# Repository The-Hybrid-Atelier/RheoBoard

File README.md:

# Start here: [Wiki](https://github.com/The-Hybrid-Atelier/RheoBoard/wiki)

- [What is REP?](https://github.com/The-Hybrid-Atelier/RheoBoard/wiki/What-is-REP)
- [Sensing Setup](https://github.com/The-Hybrid-Atelier/RheoBoard/wiki/Sensing-Setup)
- [Build options](https://github.com/The-Hybrid-Atelier/RheoBoard/wiki/Build-options)
- [Current PCB (v2) and earlier revisions](RheoBoard_PCB/README.md)

## RheoBoard

RheoBoard is open hardware for pneumatic retraction-extrusion measurements. On command, it runs a REP (retraction-extrusion pulse) and streams the pressure trace.

## License

All license notices are consolidated in [`LICENSE`](LICENSE):

- Hardware designs: CERN-OHL-W-2.0
- Firmware: MIT
- Documentation: [CC BY-SA 4.0](https://creativecommons.org/licenses/by-sa/4.0/)

RheoBoard project version 1 is certified open source hardware by the Open Source Hardware Association,
UID [US002865](https://certification.oshwa.org/us002865.html); details are on the
[Certification](https://github.com/The-Hybrid-Atelier/RheoBoard/wiki/Certification) page.
Machine-readable project metadata and the current version are in
[`okh-RheoBoard.yml`](okh-RheoBoard.yml).

## Authors

This project was created and maintained by [Cesar Torres](https://www.cearto.com) and [Charlie Vuong](https://charlie-vuong.com/) (The Hybrid Atelier at UT Arlington).

> **RheoBoard is part of [Rheoverse](https://rheoverse.cearto.com/)**, the public platform for the NSF CAREER project “Towards Interactive Sensor-Driven Tools for Exploring, Replicating, and Sharing Material Recipes” ([Award 2543683](https://www.nsf.gov/awardsearch/show-award?AWD_ID=2543683)).

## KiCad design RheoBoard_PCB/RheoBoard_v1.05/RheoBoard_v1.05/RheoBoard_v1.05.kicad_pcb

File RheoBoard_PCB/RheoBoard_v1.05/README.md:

# RheoBoard v1.05

Ordering notes for this revision are on the [BOM](https://github.com/The-Hybrid-Atelier/RheoBoard/wiki/BOM) page. Open `RheoBoard_v1.05/RheoBoard_v1.05.kicad_pro`. The main schematic and PCB use that same stem. Other schematics beside them are standalone block references or stubs, not the project hierarchy.

- Revision notes: `REVISION_NOTES.md`
- BOM: `BOM/README.md`
- Assembly and bringup: `ASSEMBLY_AND_BRINGUP.md` (button cable, GPIO map, and PCA register settings)
- Manufacturing files: `Manufacturing/README.md`
- `Archive_v1_outputs/` holds the historical v1 outputs, including the original assembly workbook `Archive_v1_outputs/BOM/BOM_RheoboardV1_JLCSMT.xlsx`

This remains an untested hardware revision. Supplier placement review and physical electrical, thermal, and mechanical qualification remain open. The maintainer accepted the retained sensor-reset and valve-voltage-margin risks for this prototype; that acceptance is not a measured hardware result or repeated-production approval. The repository DIY sketch is not verified compatible with this actuator interface.

Hardware design licensing follows the repository root LICENSE, CERN-OHL-W-2.0. Documentation is CC BY-SA 4.0.

The inner project folder was renamed from `RheoboardV1` to `RheoBoard_v1.05` on 2026-10-22. Source contents and revision are unchanged.

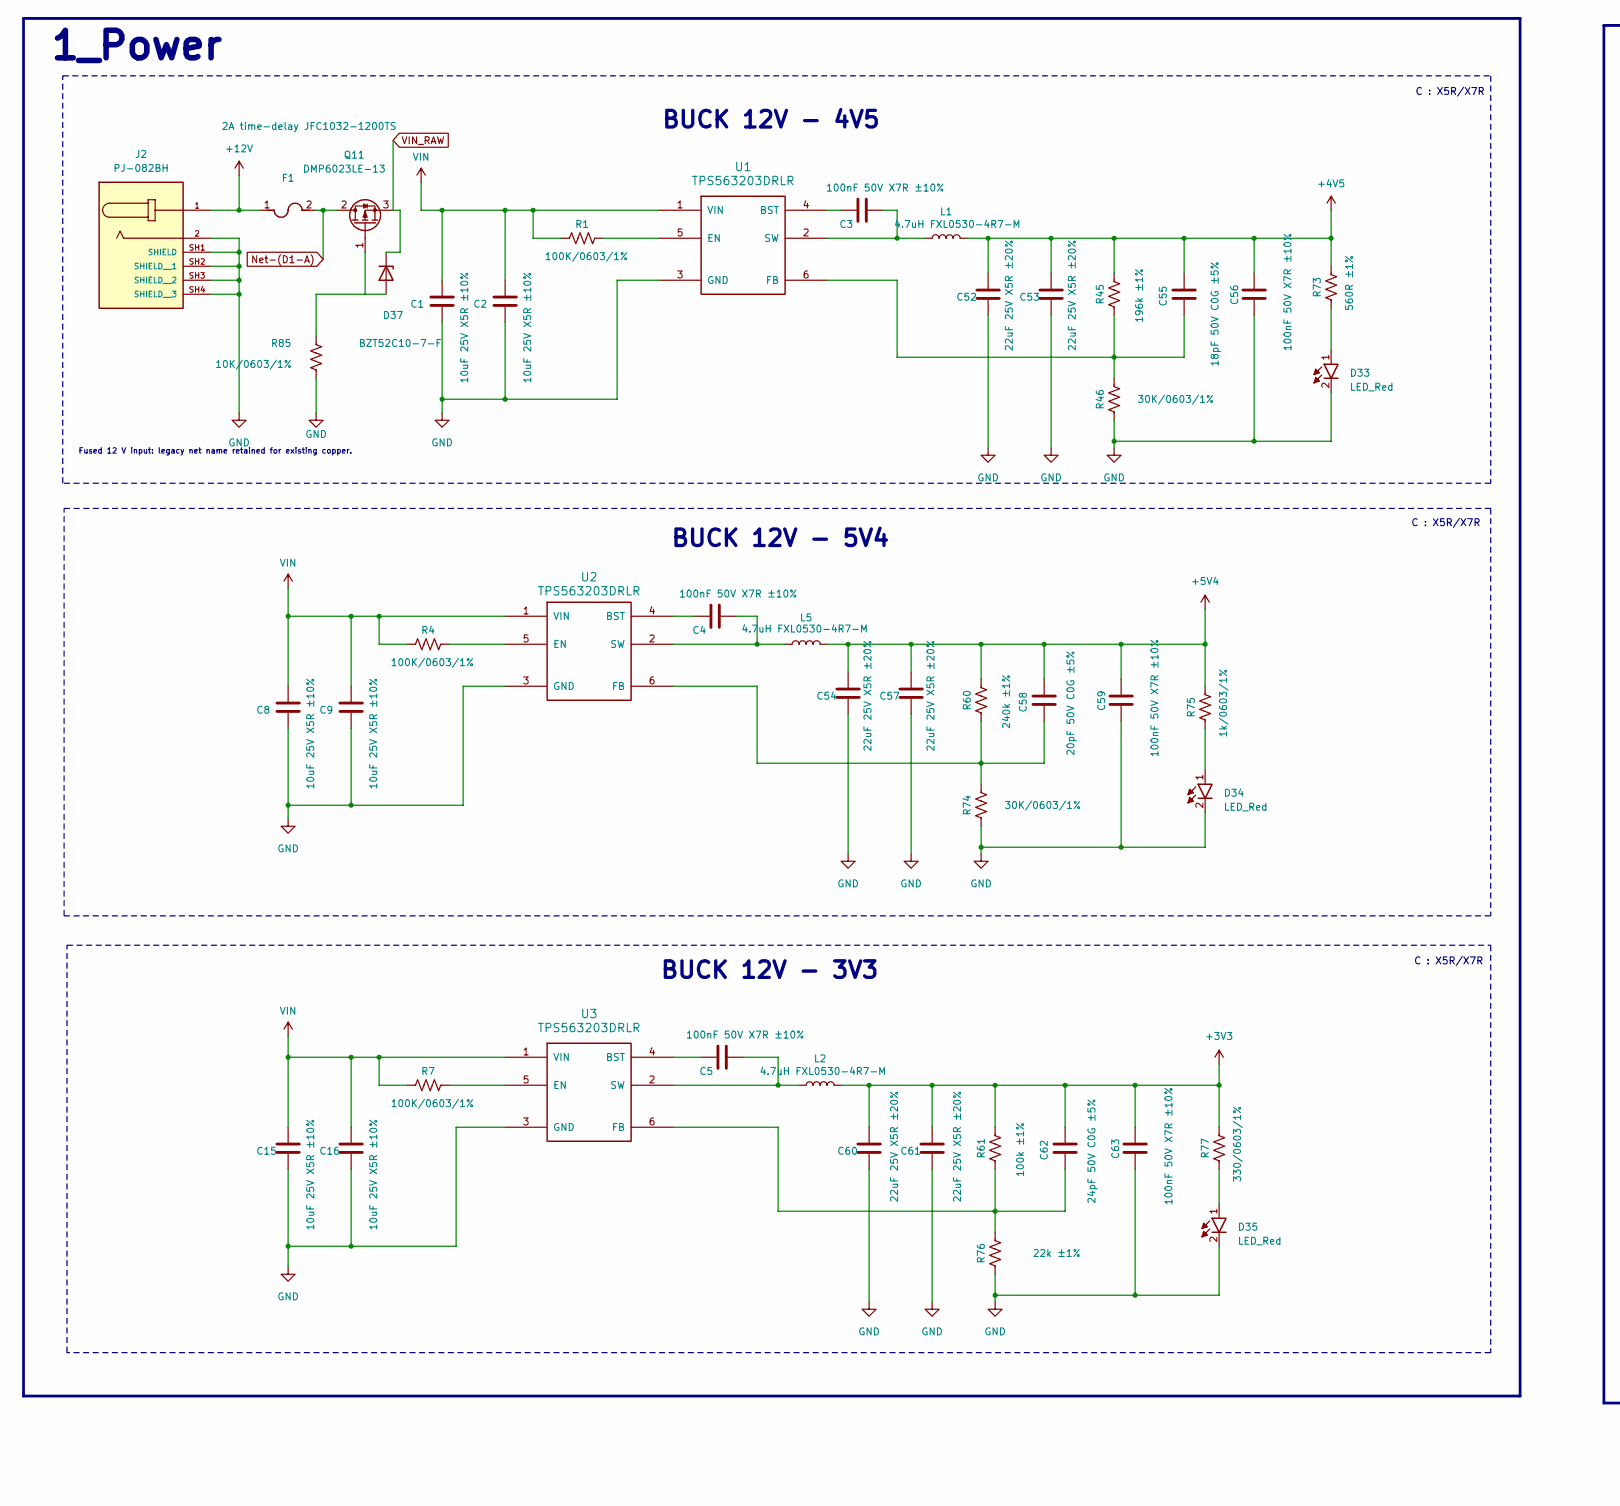
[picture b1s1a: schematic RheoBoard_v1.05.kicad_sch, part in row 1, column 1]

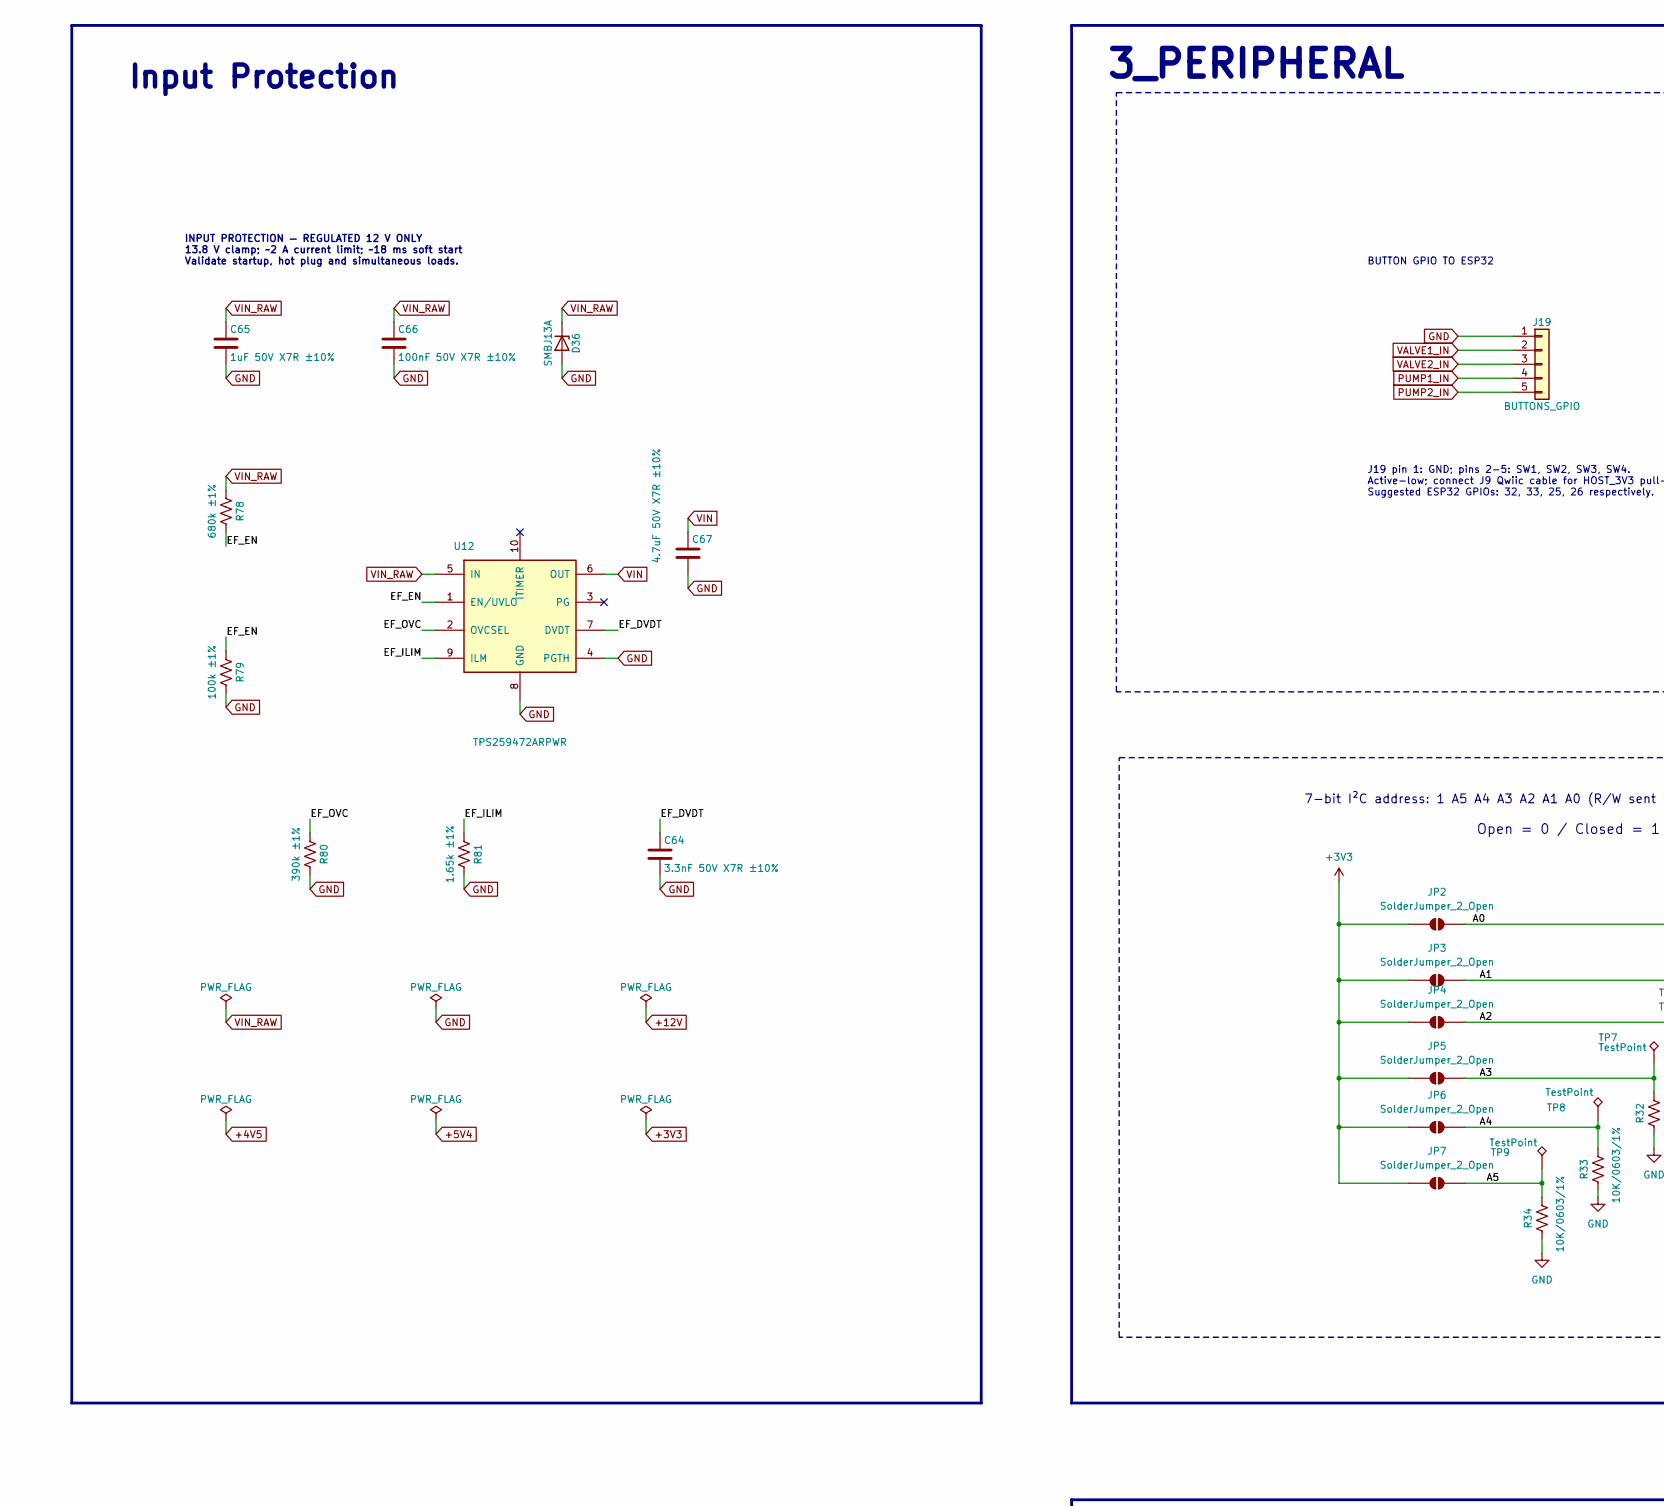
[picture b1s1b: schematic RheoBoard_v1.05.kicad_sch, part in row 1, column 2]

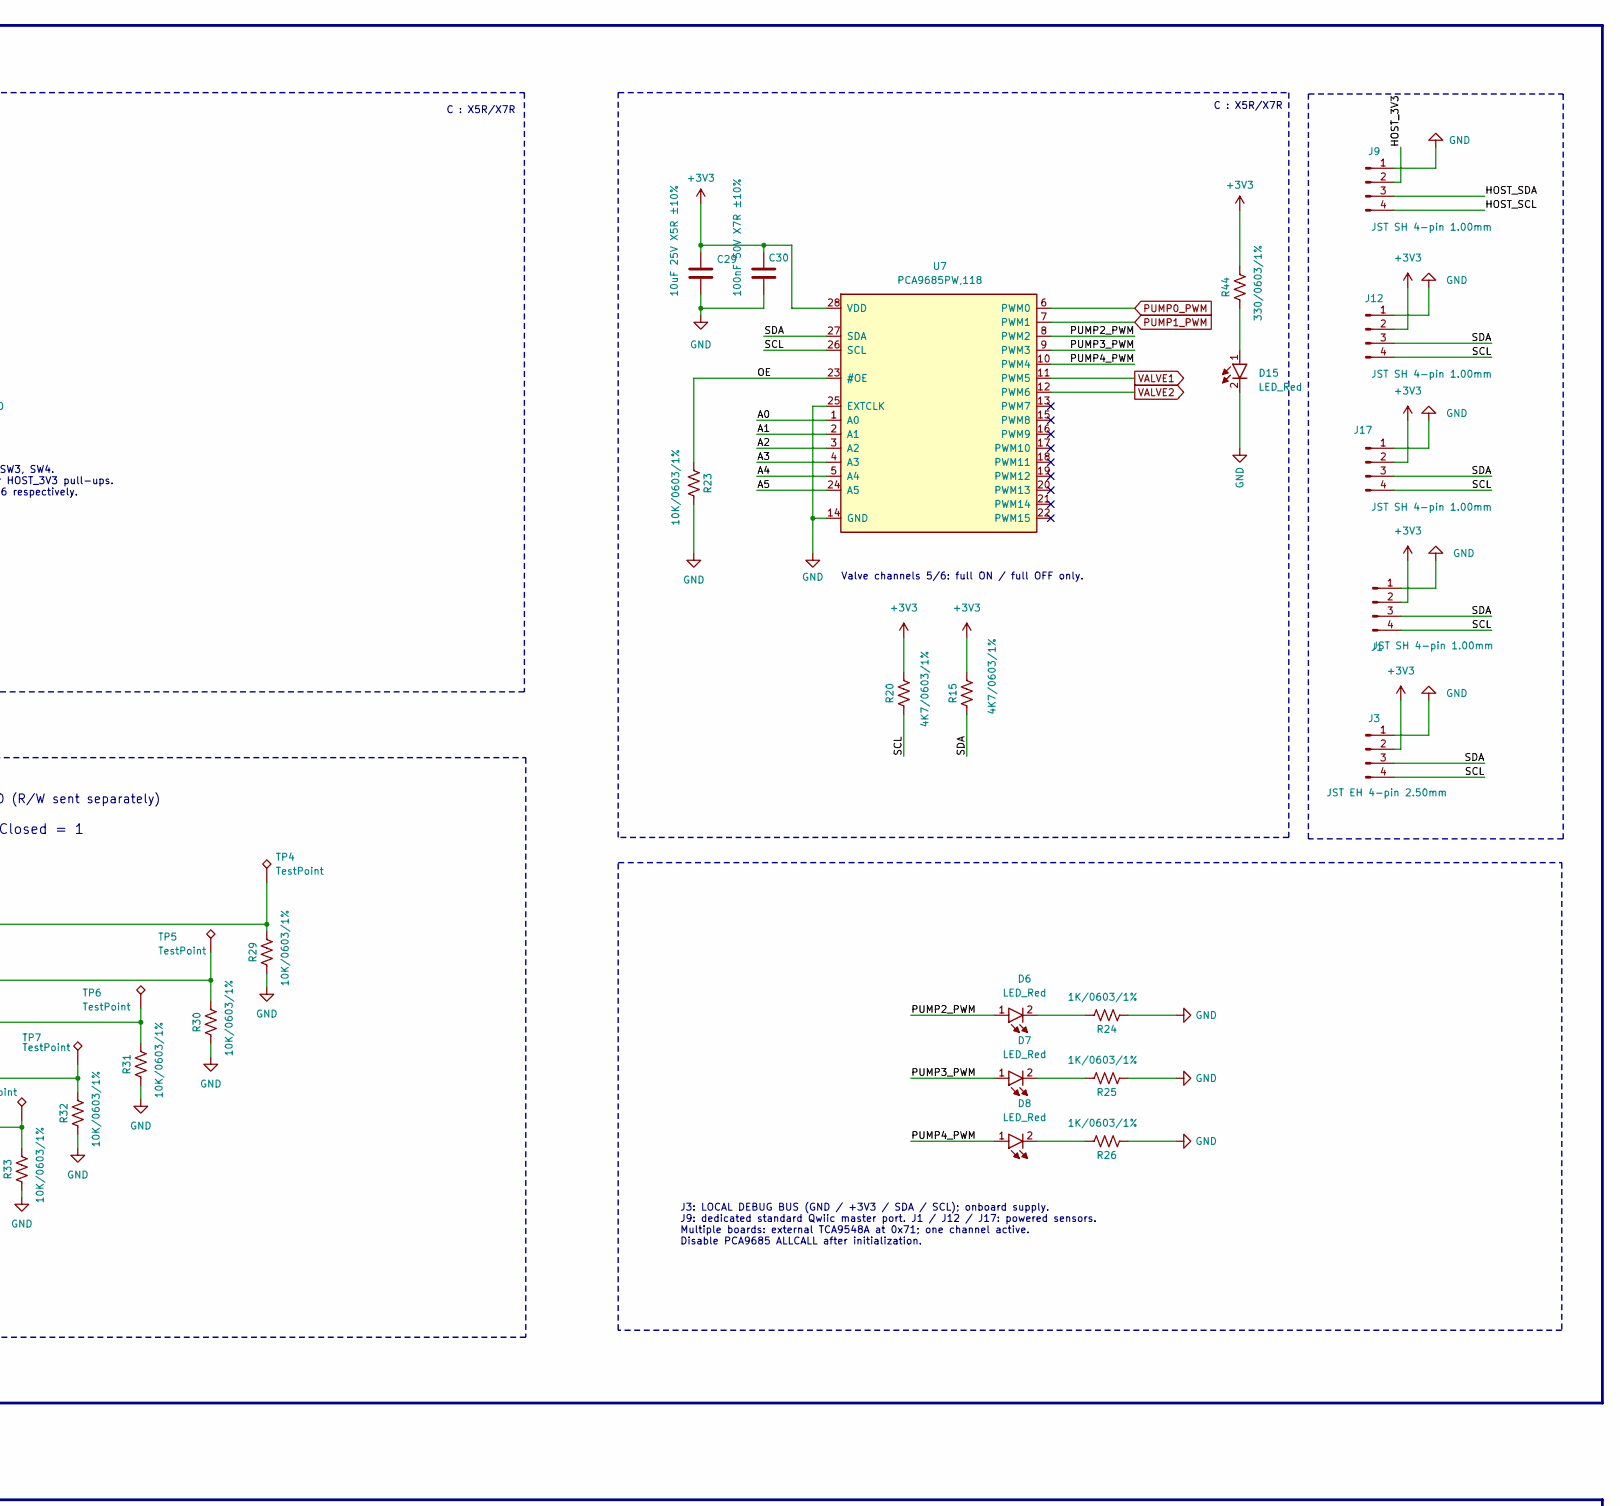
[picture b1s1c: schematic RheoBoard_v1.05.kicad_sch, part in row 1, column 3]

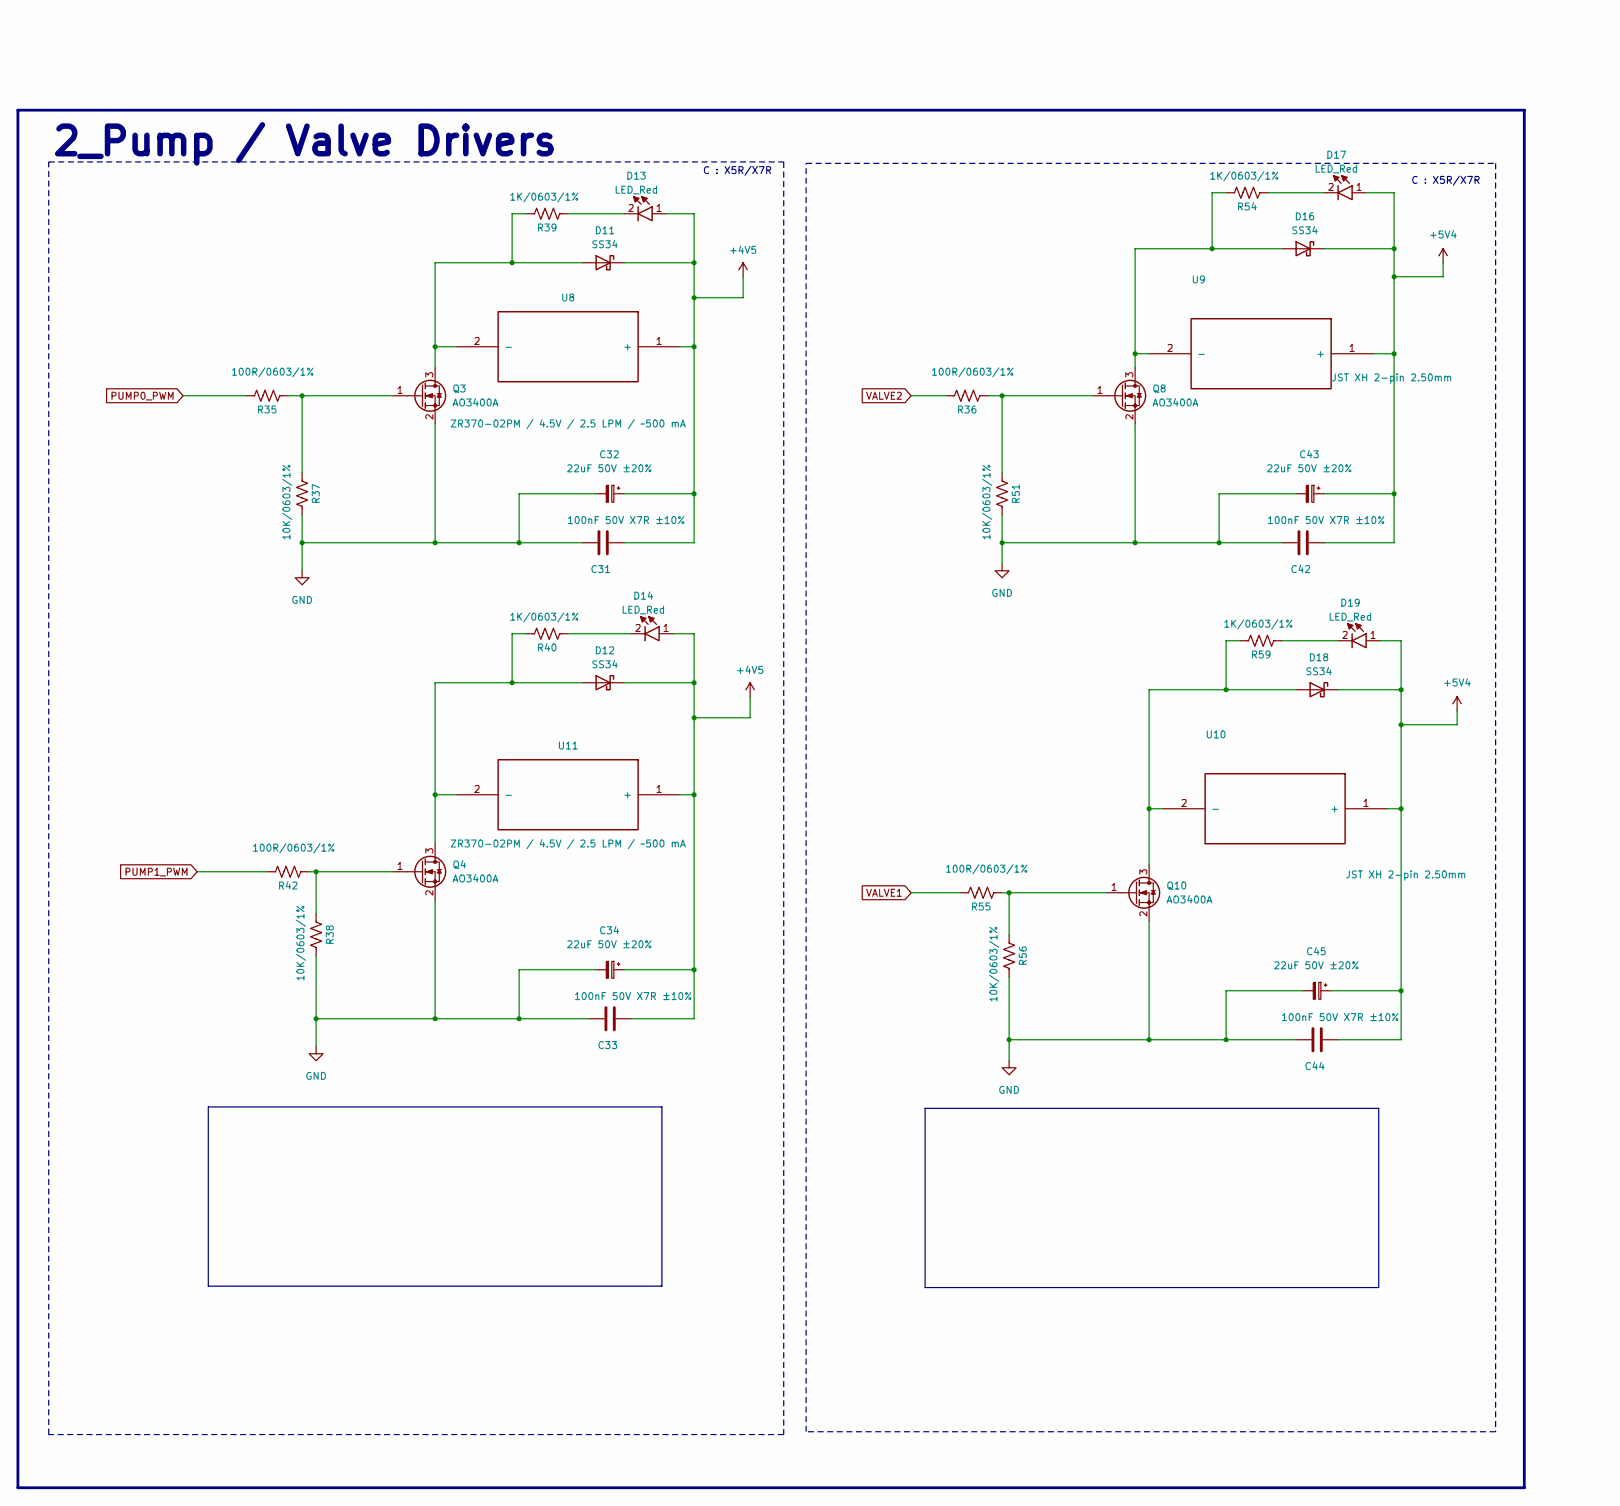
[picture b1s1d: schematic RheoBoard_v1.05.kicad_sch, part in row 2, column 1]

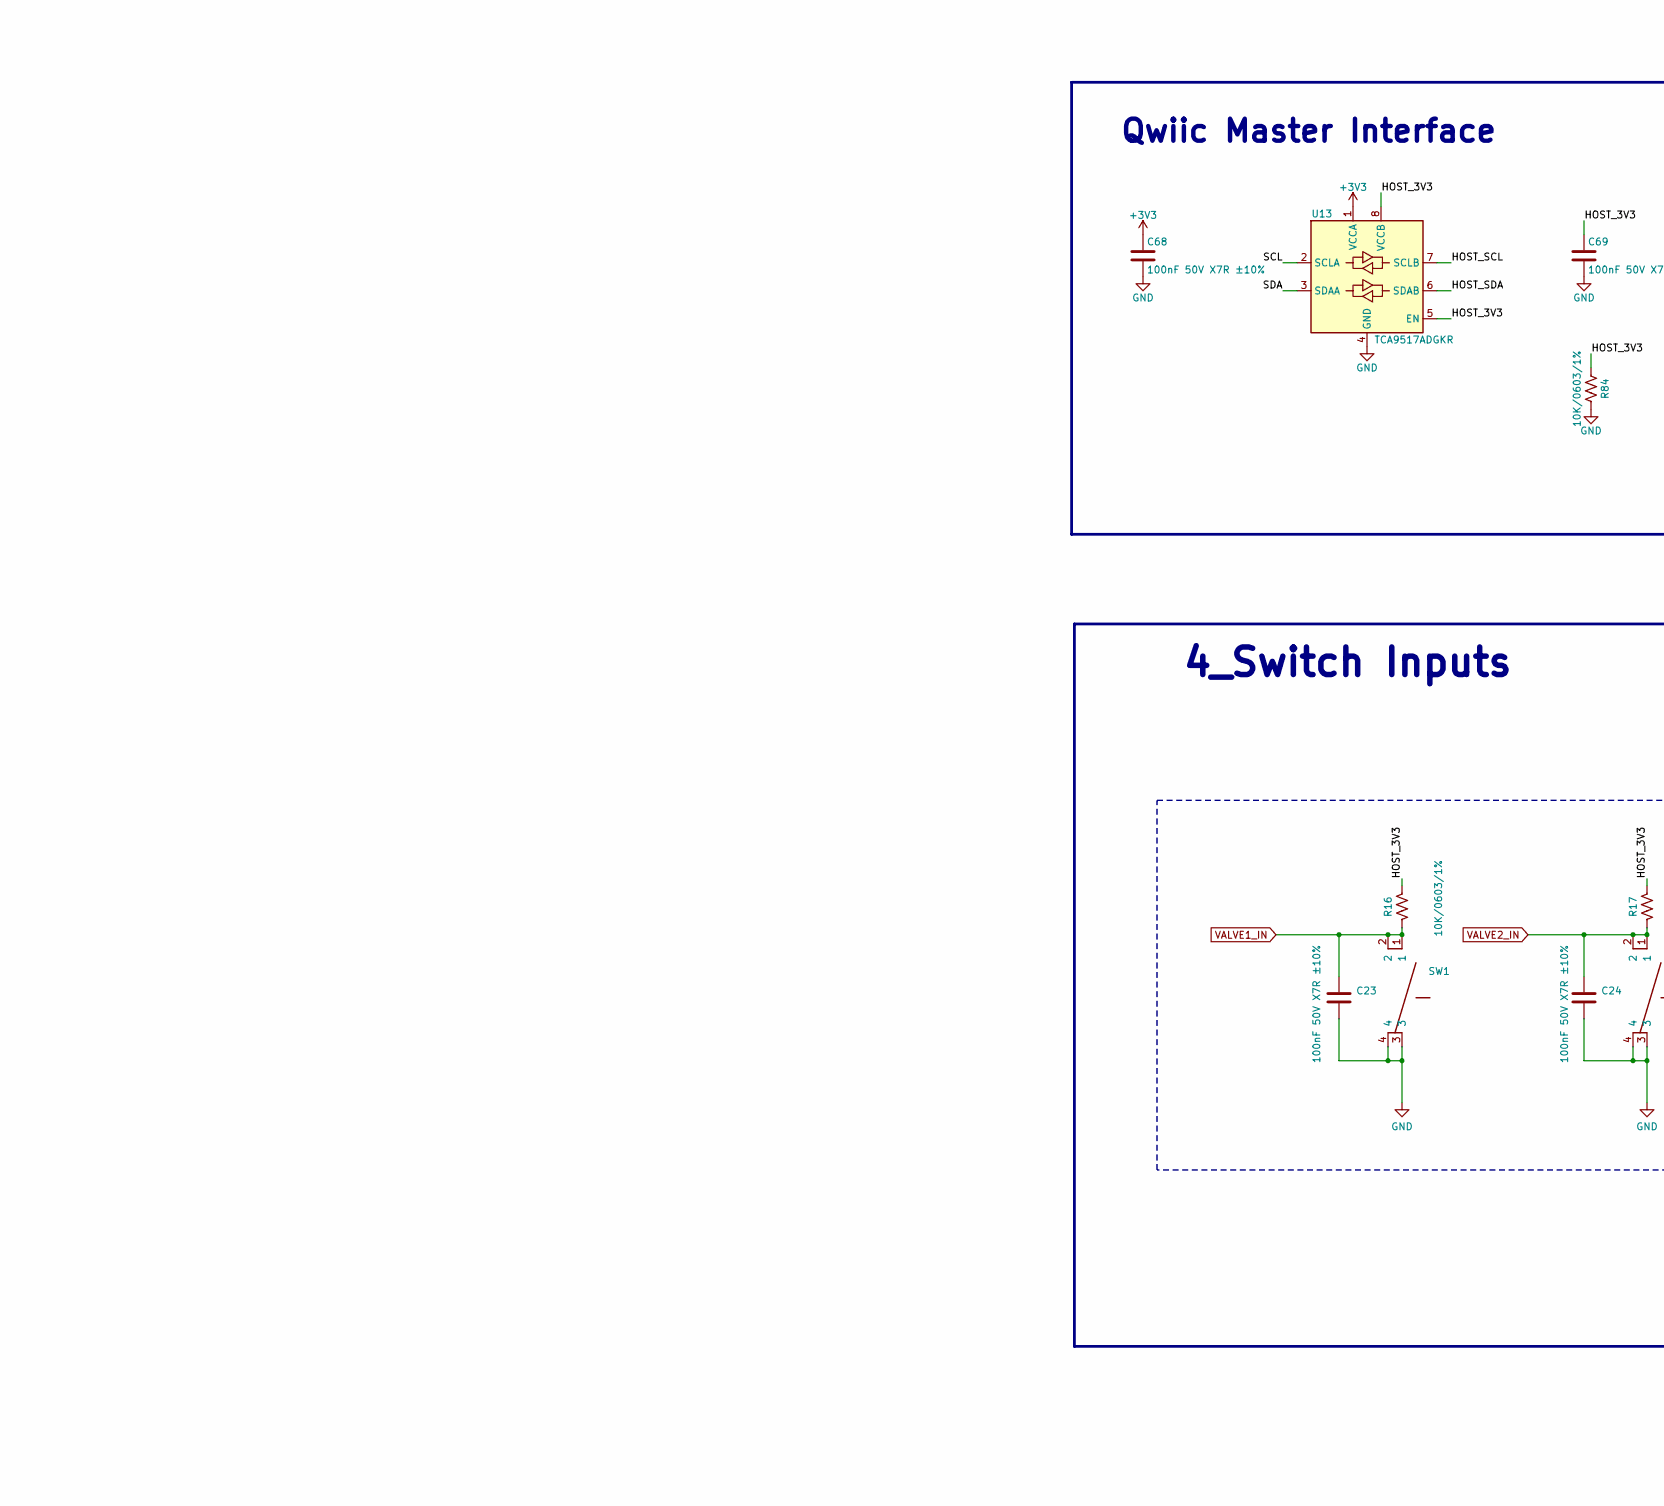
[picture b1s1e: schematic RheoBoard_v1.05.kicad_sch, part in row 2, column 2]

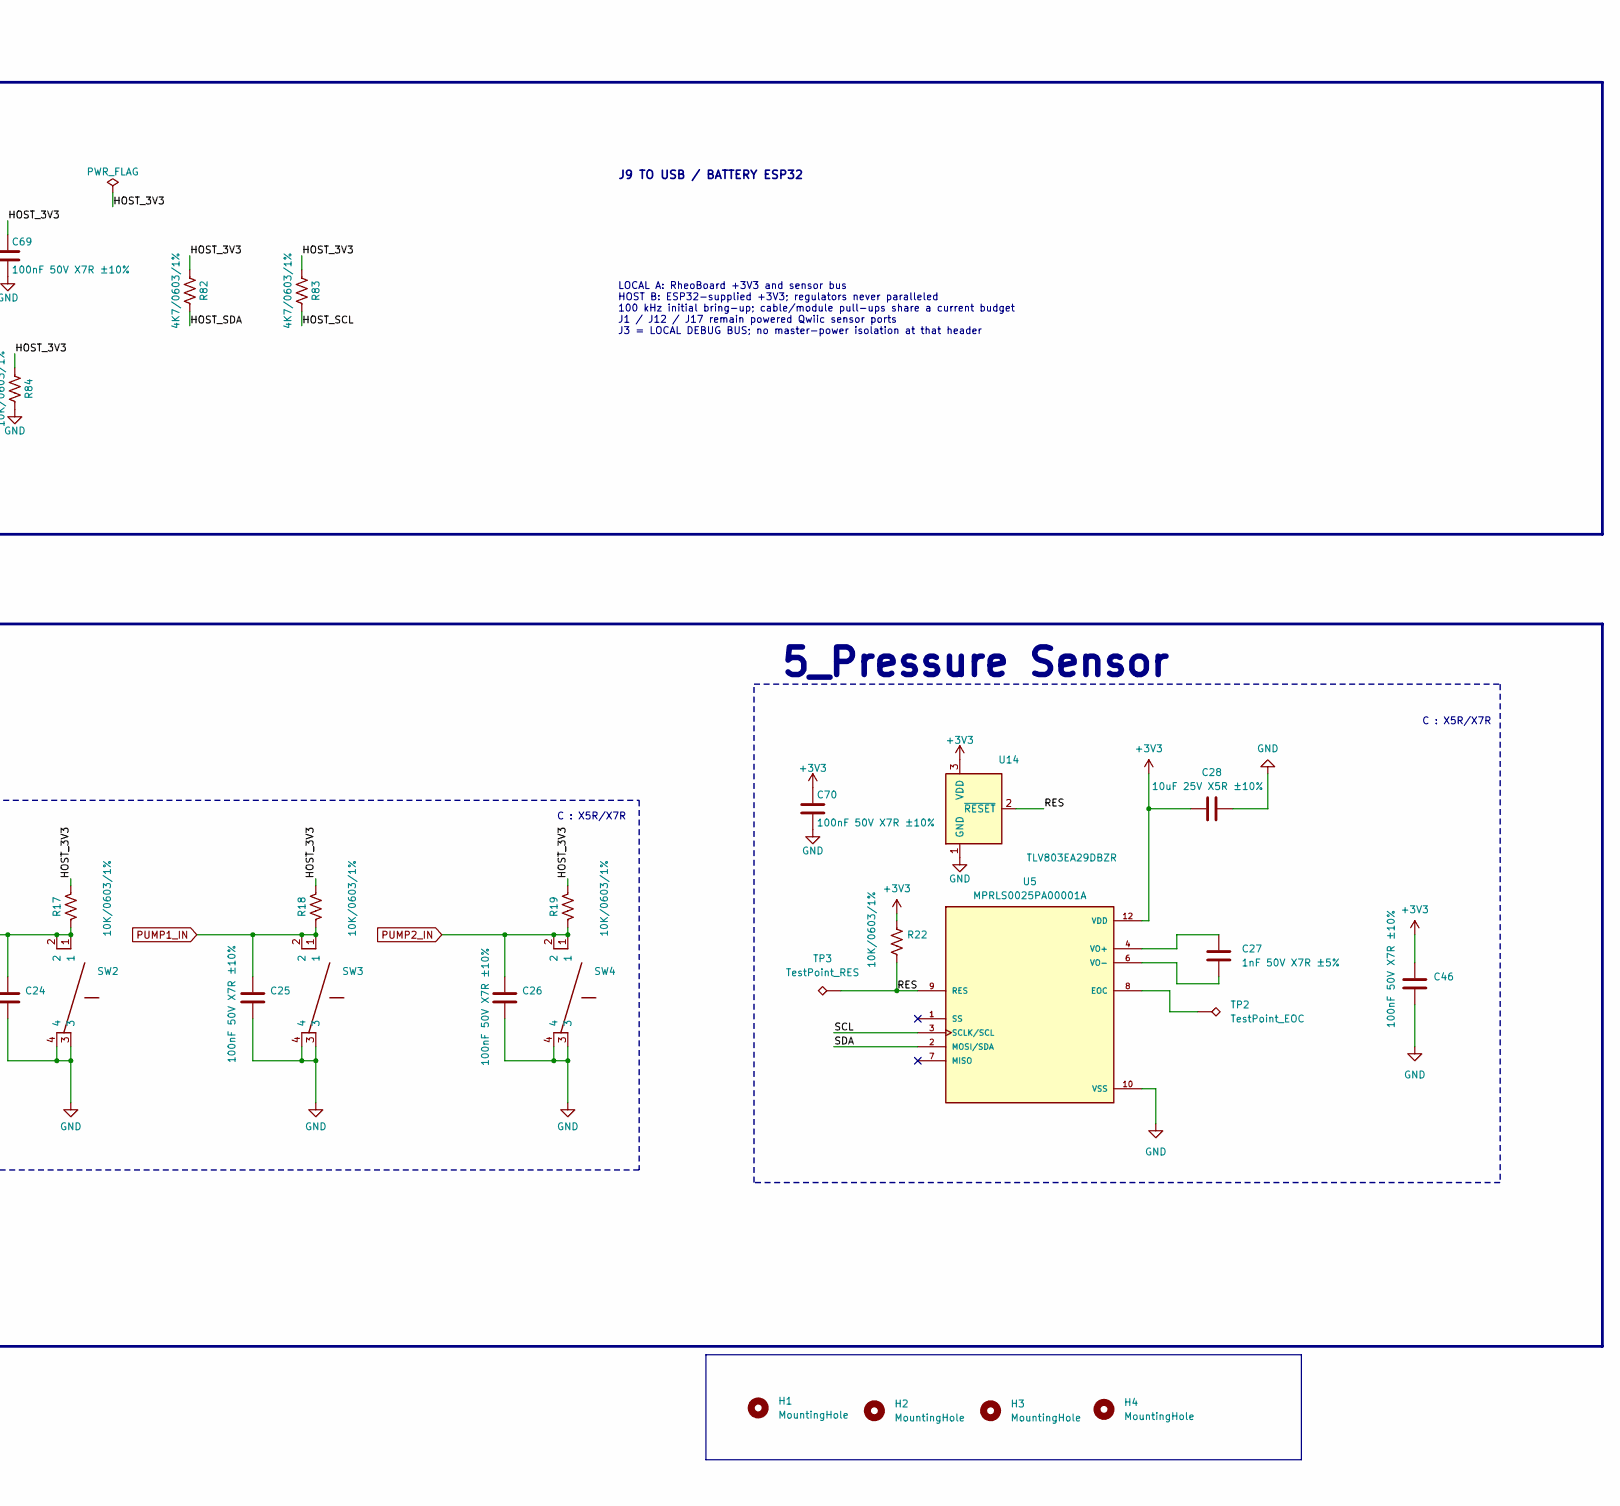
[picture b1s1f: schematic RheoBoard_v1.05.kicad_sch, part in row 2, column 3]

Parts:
C1, C2, C8, C9, C15, C16: 10uF 25V X5R ±10%; C_0805_2012Metric_Pad1.18x1.45mm_HandSolder; MPN TCC0805X5R106K250FT; LCSC C5448891
C3, C4, C5, C23, C24, C25, C26, C30, C31, C33, C42, C44, C46, C56, C59, C63, C68, C69: 100nF 50V X7R ±10%; C_0603_1608Metric_Pad1.08x0.95mm_HandSolder; MPN CC0603KRX7R9BB104; LCSC C14663
C27: 1nF 50V X7R ±5%; C_0603_1608Metric_Pad1.08x0.95mm_HandSolder; MPN TCC0603X7R102J500CT; LCSC C5360811
C28, C29: 10uF 25V X5R ±10%; C_0603_1608Metric_Pad1.08x0.95mm_HandSolder; MPN TCC0603X5R106K250CT; LCSC C7393892
C32, C34, C43, C45: 22uF 50V ±20%; CP_Elec_6.3x5.8; MPN EEEFK1H220P; LCSC C128458
C52, C53, C54, C57, C60, C61: 22uF 25V X5R ±20%; C_0805_2012Metric_Pad1.18x1.45mm_HandSolder; MPN TCC0805X5R226M250FT; LCSC C20416420
C55: 18pF 50V C0G ±5%; C_0603_1608Metric_Pad1.08x0.95mm_HandSolder; MPN CC0603JRNPO9BN180; LCSC C107040
C58: 20pF 50V C0G ±5%; C_0603_1608Metric_Pad1.08x0.95mm_HandSolder; MPN CL10C200JB8NNNC; LCSC C1648
C62: 24pF 50V C0G ±5%; C_0603_1608Metric_Pad1.08x0.95mm_HandSolder; MPN CC0603JRNPO9BN240; LCSC C107044
C64: 3.3nF 50V X7R ±10%; C_0603_1608Metric; MPN CC0603KRX7R9BB332; LCSC C107088
C65: 1uF 50V X7R ±10%; C_0805_2012Metric; MPN CC0805KKX7R9BB105; LCSC C91185
C66, C70: 100nF 50V X7R ±10%; C_0603_1608Metric; MPN CC0603KRX7R9BB104; LCSC C14663
C67: 4.7uF 50V X7R ±10%; C_1206_3216Metric; MPN CC1206KKX7R9BB475; LCSC C132170
D6, D7, D8, D13, D14, D15, D17, D19: LED_Red; LED_SZYY0603R_A1_K2_HandSolder; MPN SZYY0603R; LCSC C434419
D11, D12, D16, D18: SS34; D_SMA; MPN SS34; LCSC C115205
D33, D34, D35: LED_Red; LED_SZYY0603R_A1_K2_Nominal; MPN SZYY0603R; LCSC C434419
D36: SMBJ13A; D_SMB; MPN SMBJ13A; LCSC C151252
D37: BZT52C10-7-F; D_SOD-123; MPN BZT52C10-7-F; LCSC C155227
F1: 2A time-delay JFC1032-1200TS; Fuse_JDT_JFC1032TS_10.25x3.2mm; MPN JFC1032-1200TS; LCSC C53035082
H1, H2, H3, H4: MountingHole; MountingHole_3.5mm_Pad
J1, J9, J12, J17: JST SH 4-pin 1.00mm; JST_SH_SM04B-SRSS-TB_1x04-1MP_P1.00mm_Horizontal; MPN SM04B-SRSS-TB(LF)(SN); LCSC C160404
J2: PJ-082BH; PARTREV 1.06; LCSC C3094233
J3: JST EH 4-pin 2.50mm; JST_EH_B4B-EH-A_1x04_P2.50mm_Vertical_DFM; MPN B4B-EH-A(LF)(SN); LCSC C160258
J19: BUTTONS_GPIO; PinHeader_1x05_P2.54mm_Vertical; MPN B-2100S05P-A110; LCSC C124379
JP2, JP3, JP4, JP5, JP6, JP7: SolderJumper_2_Open; SolderJumper-2_P1.3mm_Open_Pad1.0x1.5mm
L1, L2, L5: 4.7uH FXL0530-4R7-M; L_Changjiang_FXL0530; MPN FXL0530-4R7-M; LCSC C177246
Q3: AO3400A; AO3400A_Pin1Offset; MPN AO3400A; LCSC C20917
Q4, Q8, Q10: AO3400A; MPN AO3400A; LCSC C20917
Q11: DMP6023LE-13; SOT-223-3_TabPin2_DFM; MPN DMP6023LE-13; LCSC C154901
R1, R4, R7: 100K/0603/1%; R_0603_1608Metric_Pad0.98x0.95mm_HandSolder; MPN 0603WAF1003T5E; LCSC C25803
R15, R20, R82, R83: 4K7/0603/1%; R_0603_1608Metric_Pad0.98x0.95mm_HandSolder; MPN 0603WAF4701T5E; LCSC C23162
R16, R17, R18, R19, R22, R23, R29, R30, R31, R32, R33, R34, R37, R38, R51, R56, R84, R85: 10K/0603/1%; R_0603_1608Metric_Pad0.98x0.95mm_HandSolder; MPN 0603WAF1002T5E; LCSC C25804
R24, R25, R26, R39, R40, R54, R59: 1K/0603/1%; R_0603_1608Metric_Pad0.98x0.95mm_HandSolder; MPN 0603WAF1001T5E; LCSC C21190
R35, R36, R42, R55: 100R/0603/1%; R_0603_1608Metric_Pad0.98x0.95mm_HandSolder; MPN 0603WAF1000T5E; LCSC C22775
R44, R77: 330/0603/1%; R_0603_1608Metric_Pad0.98x0.95mm_HandSolder; MPN 0603WAF3300T5E; LCSC C23138
R45: 196k ±1%; R_0603_1608Metric_Pad0.98x0.95mm_HandSolder; MPN CRCW0603196KFKEA; LCSC C4203218
R46, R74: 30K/0603/1%; R_0603_1608Metric_Pad0.98x0.95mm_HandSolder; MPN 0603WAF3002T5E; LCSC C22984
R60: 240k ±1%; R_0603_1608Metric_Pad0.98x0.95mm_HandSolder; MPN 0603WAF2403T5E; LCSC C4197
R61: 100k ±1%; R_0603_1608Metric_Pad0.98x0.95mm_HandSolder; MPN 0603WAF1003T5E; LCSC C25803
R73: 560R ±1%; R_0603_1608Metric_Pad0.98x0.95mm_HandSolder; MPN 0603WAF5600T5E; LCSC C23204
R75: 1k/0603/1%; R_0603_1608Metric_Pad0.98x0.95mm_HandSolder; MPN 0603WAF1001T5E; LCSC C21190
R76: 22k ±1%; R_0603_1608Metric_Pad0.98x0.95mm_HandSolder; MPN 0603WAF2202T5E; LCSC C31850
R78: 680k ±1%; R_0603_1608Metric; MPN 0603WAF6803T5E; LCSC C25822
R79: 100k ±1%; R_0603_1608Metric; MPN 0603WAF1003T5E; LCSC C25803
R80: 390k ±1%; R_0603_1608Metric; MPN HP03W5F3903T5E; LCSC C2759410
R81: 1.65k ±1%; R_0603_1608Metric; MPN 0603WAF1651T5E; LCSC C22845
SW1, SW2, SW3, SW4: TL3301NF160QG/P010515; Tactile_Switch_4pad; MPN TL3301NF160QG/P010515; LCSC C273527
TP2: TestPoint_EOC; TestPoint_Plated_D1.0_Drill0.5
TP3: TestPoint_RES; TestPoint_Plated_D1.0_Drill0.5
TP4, TP5, TP6, TP7, TP8, TP9: TestPoint; TestPoint_Plated_D1.0_Drill0.5
U1, U2, U3: TPS563203DRLR; MPN TPS563203DRLR; LCSC C22445512
U5: MPRLS0025PA00001A; PARTREV 03/18; LCSC C3257154
U7: PCA9685PW,118; PCA9685; MPN PCA9685PW,118; LCSC C2678753
U8, U11: ZR370-02PM / 4.5V / 2.5 LPM / ~500 mA; PUMP; MPN ZR370-02PM
U9, U10: JST XH 2-pin 2.50mm; VALVE_v105; MPN B2B-XH-A(LF)(SN); LCSC C158012
U12: TPS259472ARPWR; TI_RPW0010A_VQFN-HR_2x2mm; MPN TPS259472ARPWR; LCSC C3662789
U13: TCA9517ADGKR; TI_DGK0008A_VSSOP_3x3mm_P0.65mm; MPN TCA9517ADGKR; LCSC C201698
U14: TLV803EA29DBZR; SOT-23; MPN TLV803EA29DBZR; LCSC C1852114

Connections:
+3V3: C28.1, C29.1, C30.1, C46.1, C60.1, C61.1, C62.1, C63.1, C68.1, C70.1, J1.2, J3.2, J12.2, J17.2, JP2.1 (A), JP3.1 (A), JP4.1 (A), JP5.1 (A), JP6.1 (A), JP7.1 (A), L2.2, R15.2, R20.2, R22.1, R44.2, R61.2, R77.2, U5.12 (VDD), U7.28 (VDD), U13.1 (VCCA), U14.3 (VDD)
+4V5: C31.2, C32.1, C33.2, C34.1, C52.1, C53.1, C55.1, C56.1, D11.1 (K), D12.1 (K), D13.1 (A), D14.1 (A), L1.2, R45.2, R73.2, U8.1 (+), U11.1 (+)
+5V4: C42.2, C43.1, C44.2, C45.1, C54.1, C57.1, C58.1, C59.1, D16.1 (K), D17.1 (A), D18.1 (K), D19.1 (A), L5.2, R60.2, R75.2, U9.1 (+), U10.1 (+)
+12V: F1.1, J2.1
/A0: JP2.2 (B), R29.2, TP4.1 (1_1), U7.1 (A0)
/A1: JP3.2 (B), R30.2, TP5.1 (1_1), U7.2 (A1)
/A2: JP4.2 (B), R31.2, TP6.1 (1_1), U7.3 (A2)
/A3: JP5.2 (B), R32.2, TP7.1 (1_1), U7.4 (A3)
/A4: JP6.2 (B), R33.2, TP8.1 (1_1), U7.5 (A4)
/A5: JP7.2 (B), R34.2, TP9.1 (1_1), U7.24 (A5)
/EF_DVDT: C64.1, U12.7 (DVDT)
/EF_EN: R78.2, R79.1, U12.1 (EN/UVLO)
/EF_ILIM: R81.1, U12.9 (ILM)
/EF_OVC: R80.1, U12.2 (OVCSEL)
/HOST_3V3: C69.1, J9.2, R16.1, R17.1, R18.1, R19.1, R82.1, R83.1, R84.1, U13.5 (EN), U13.8 (VCCB)
/HOST_SCL: J9.4, R83.2, U13.7 (SCLB)
/HOST_SDA: J9.3, R82.2, U13.6 (SDAB)
/OE: R23.1, U7.23 (#OE)
/PUMP2_PWM: D6.1 (A), U7.8 (PWM2)
/PUMP3_PWM: D7.1 (A), U7.9 (PWM3)
/PUMP4_PWM: D8.1 (A), U7.10 (PWM4)
/RES: R22.2, TP3.1 (1_1), U5.9 (RES), U14.2 (~RESET)
/SCL: J1.4, J3.4, J12.4, J17.4, R20.1, U5.3 (SCLK/SCL), U7.26 (SCL), U13.2 (SCLA)
/SDA: J1.3, J3.3, J12.3, J17.3, R15.1, U5.2 (MOSI/SDA), U7.27 (SDA), U13.3 (SDAA)
GND: C1.2, C2.2, C8.2, C9.2, C15.2, C16.2, C23.2, C24.2, C25.2, C26.2, C28.2, C29.2, C30.2, C31.1, C32.2, C33.1, C34.2, C42.1, C43.2, C44.1, C45.2, C46.2, C52.2, C53.2, C54.2, C56.2, C57.2, C59.2, C60.2, C61.2, C63.2, C64.2, C65.2, C66.2, C67.2, C68.2, C69.2, C70.2, D15.2 (K), D33.2 (K), D34.2 (K), D35.2 (K), D36.2 (A), J1.1, J2.2, J2.SH1 (SHIELD), J2.SH2 (SHIELD__1), J2.SH3 (SHIELD__2), J2.SH4 (SHIELD__3), J3.1, J9.1, J12.1, J17.1, J19.1, Q3.2 (S), Q4.2 (S), Q8.2 (S), Q10.2 (S), R23.2, R24.1, R25.1, R26.1, R29.1, R30.1, R31.1, R32.1, R33.1, R34.1, R37.2, R38.2, R46.1, R51.2, R56.2, R74.1, R76.1, R79.2, R80.2, R81.2, R84.2, R85.2, SW1.3, SW1.4, SW2.3, SW2.4, SW3.3, SW3.4, SW4.3, SW4.4, U1.3 (GND), U2.3 (GND), U3.3 (GND), U5.10 (VSS), U7.14 (GND), U7.25 (EXTCLK), U12.4 (PGTH), U12.8 (GND), U13.4 (GND), U14.1 (GND)
unnamed: F1.2, Q11.2 (D)
unnamed: D6.2 (K), R24.2
unnamed: D7.2 (K), R25.2
unnamed: D8.2 (K), R26.2
unnamed: D11.2 (A), Q3.3 (D), R39.2, U8.2 (-)
unnamed: D12.2 (A), Q4.3 (D), R40.2, U11.2 (-)
unnamed: D13.2 (K), R39.1
unnamed: D14.2 (K), R40.1
unnamed: D15.1 (A), R44.1
unnamed: D16.2 (A), Q8.3 (D), R54.2, U9.2 (-)
unnamed: D17.2 (K), R54.1
unnamed: D18.2 (A), Q10.3 (D), R59.2, U10.2 (-)
unnamed: D19.2 (K), R59.1
unnamed: D33.1 (A), R73.1
unnamed: D34.1 (A), R75.1
unnamed: D35.1 (A), R77.1
unnamed: D37.2 (A), Q11.1 (G), R85.1
unnamed: Q3.1 (G), R35.1, R37.1
unnamed: Q4.1 (G), R38.1, R42.1
unnamed: Q8.1 (G), R36.1, R51.1
unnamed: Q10.1 (G), R55.1, R56.1
unnamed: C3.1, U1.4 (BST)
unnamed: R1.2, U1.5 (EN)
unnamed: C55.2, R45.1, R46.2, U1.6 (FB)
unnamed: C3.2, L1.1, U1.2 (SW)
unnamed: C4.1, U2.4 (BST)
unnamed: R4.2, U2.5 (EN)
unnamed: C58.2, R60.1, R74.2, U2.6 (FB)
unnamed: C4.2, L5.1, U2.2 (SW)
unnamed: C5.1, U3.4 (BST)
unnamed: R7.2, U3.5 (EN)
unnamed: C62.2, R61.1, R76.2, U3.6 (FB)
unnamed: C5.2, L2.1, U3.2 (SW)
unnamed: TP2.1 (1_1), U5.8 (EOC)
unnamed: C27.1, U5.4 (VO+)
unnamed: C27.2, U5.6 (VO-)
PUMP0_PWM: R35.2, U7.6 (PWM0)
PUMP1_IN: C25.1, J19.4, R18.2, SW3.1, SW3.2
PUMP1_PWM: R42.2, U7.7 (PWM1)
PUMP2_IN: C26.1, J19.5, R19.2, SW4.1, SW4.2
VALVE1: R55.2, U7.11 (PWM5)
VALVE1_IN: C23.1, J19.2, R16.2, SW1.1, SW1.2
VALVE2: R36.2, U7.12 (PWM6)
VALVE2_IN: C24.1, J19.3, R17.2, SW2.1, SW2.2
VIN: C1.1, C2.1, C8.1, C9.1, C15.1, C16.1, C67.1, R1.1, R4.1, R7.1, U1.1 (VIN), U2.1 (VIN), U3.1 (VIN), U12.6 (OUT)
VIN_RAW: C65.1, C66.1, D36.1 (K), D37.1 (K), Q11.3 (S), R78.1, U12.5 (IN)

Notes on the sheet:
2_Pump / Valve Drivers
3_PERIPHERAL
BUTTON GPIO TO ESP32
Fused 12 V input: legacy net name retained for existing copper.
BUCK 12V - 3V3
C : X5R/X7R
BUCK 12V - 5V4
Open = 0 / Closed = 1
Qwiic Master Interface
J19 pin 1: GND; pins 2-5: SW1, SW2, SW3, SW4. Active-low; connect J9 Qwiic cable for HOST_3V3 pull-ups. Suggested ESP32 GPIOs: 32, 33, 25, 26 respectively.
Input Protection
J9 TO USB / BATTERY ESP32
J3: LOCAL DEBUG BUS (GND / +3V3 / SDA / SCL); onboard supply. J9: dedicated standard Qwiic master port. J1 / J12 / J17: powered sensors. Multiple boards: external TCA9548A at 0x71; one channel active. Disable PCA9685 ALLCALL after initialization.
4_Switch Inputs
7-bit I²C address: 1 A5 A4 A3 A2 A1 A0 (R/W sent separately)
LOCAL A: RheoBoard +3V3 and sensor bus HOST B: ESP32-supplied +3V3; regulators never paralleled 100 kHz initial bring-up; cable/module pull-ups share a current budget J1 / J12 / J17 remain powered Qwiic sensor ports J3 = LOCAL DEBUG BUS; no master-power isolation at that header
5_Pressure Sensor
BUCK 12V - 4V5
INPUT PROTECTION — REGULATED 12 V ONLY 13.8 V clamp; ~2 A current limit; ~18 ms soft start Validate startup, hot plug and simultaneous loads.
1_Power
Valve channels 5/6: full ON / full OFF only.
